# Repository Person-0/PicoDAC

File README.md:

# **PicoDAC**

<br>

*USB-C to 3.5mm HiFi mini DAC*

Fully custom PCB and 3D printed case.

## Design

### Preview Images
Note that a specially cut transparent acrylic sheet will be used as the top lid of the main PCB case which will be superglued to part of the case that is non-detachable.

The main PCB case also requires [this 2.5X8 screw](https://sharvielectronics.com/product/m2-5x8mm-phillips-head-mounting-screw-stainless-steel/) that will be used to attach the detachable part with the non-detachable part.

As for the case of the board - 2, since it really is just two directly connected USB-C plugs, the top and bottom part of the case will be glued together after seating the board-2 PCB inside it properly (after testing it).

<br>

All the design files are available in the [CAD folder](./CAD/).<br>
Exported STEP files for 3d-printing are available in [/CAD/exports](./CAD/exports/).

> Also note that the files:<br> 
> [1_PicoDAC_Case_DetachablePart.step](./CAD/exports/1_PicoDAC_Case_DetachablePart.step)<br>
> [2_PicoDAC_Case_Main.step](./CAD/exports/2_PicoDAC_Case_Main.step)<br>
> [3_board2_top_case.step](./CAD/exports/3_board2_top_case.step)<br>
> [4_board2_bottom_case.step](./CAD/exports/4_board2_bottom_case.step)<br>
> need to be printed as separate bodies.<br>
> All these files are also available in `.stl` format inside the [CAD/exports/stl_files](./CAD/exports/stl_files/) directory.

## **Motivation**

I recently bought a cheap USB-C to 3.5mm DAC and it was working perfectly fine until it broke.

I use my phone in bed a lot (yes i know this is a bad habit) vertically with the bottom of my phone resting on my chest. Since the USB-C port is at the bottom of my phone, anything connected to it has to do the heavy lifting of keeping the phone upright.

Naturally, the red part I've highlighted in the image slowly got bent and broke :(

To fix this issue, learn more about audio electronics, engineer a cool device and also make a higher-quality DAC in the process, I've started this project.

## **Hardware**
Main hardware components are:
- 1x CS43131-CNZR (A high-performance, 32-bit resolution, stereo audio DAC that supports up to 384-kHz sampling frequency with integrated low-noise ground-centered headphone amplifiers.): [LCSC part](https://www.lcsc.com/product-detail/C965907.html)
- XIAO RP2350 instead of the 2040 as it has integrated fractional dividers (also see: [this git issue](https://github.com/raspberrypi/pico-sdk/issues/1924))
- 9x SK6812 RGB LEDs for music level visualization

> **[View complete BOM](#bom)**

PCB Preview:

The complete schematics look like:

**Main Board:**

**Board 2:**

> Note that the PCB and schematic files can be opened using KiCAD. They are located in the `/hardware/PicoDAC` directory inside this repository.

Steps for viewing the PCB schematics and layout:
- Open KiCAD
- Click **File** (top left) >> **Open Project**
- Navigate to the the repository's saved destination,
- Open **/hardware/PicoDAC** directory
- Select the file `PicoDAC.kicad_pro`

## **Firmware**
*Checkout the [firmware directory](./firmware/) for the firmware README.md file and current status. It contains building, flashing instructions and also some special notes that might help with the process.*

## Ordering Parts, PCB/PCBA

I will be using JLCPCB along with their PCB Assembly service to get this PCB built assembled as it is the cheapest and best option available in my region.

Other than that, the only extra part is the **XIAO RP2350** MCU which is available on [robu.in](https://robu.in/).

> Note that the following PCB, PCBA costs are for 5 PCBs out of which 2 are assembled (this is the MOQ for JLCPCB) and also I have used basic components instead of extended wherever possible to reduce costs. 

### **BOM**
---

| S.No | Name                                 | Description                                        | Qty | Product URL                                                                     | Effective Cost ($) |
| ---: | ------------------------------------ | -------------------------------------------------- | --: | ------------------------------------------------------------------------------- | -----------------: |
|    1 | JLCPCB_PCB                           | PCB                                                |   1 | ~                                                                               |               7.00 |
|    2 | JLCPCB_Assembly                      | PCB Assembly                                       |   1 | ~                                                                               |              68.03 |
|    3 | JLCPCB_Shipping                      | Lowest price shipping: UPS Worldwide Express Saver |   1 | ~                                                                               |               9.10 |
|    4 | JLCPCB_Coupons                       | ~                                                  |   1 | ~                                                                               |             -10.00 |
|    5 | SeeedStudio XIAO RP2350              | MCU: XIAO RP2350                                   |   1 | [robu.in/...](https://robu.in/product/seeedstudio-xiao-rp2350-raspberry-pi-rp2350/) |               8.69 |
|    6 | Shipping for SeeedStudio XIAO RP2350 | Standard Shipping for XIAO RP2350                           |   1 | ~ |               0.51 |
|    5 | Acrylic Lid for Main Case            | Acrylic Laser Cutout (Qty = 2 as cost per piece is below 80INR and robu.in requires minimum cost to be atleast 80INR for non-metal laser cutting service order)                                  |   2 | ~ |               1.63 |
|    6 | Shipping for Acrylic Lid | Standard Shipping for Acrylic Lid                           |   1 | ~ |               0.51 |
|      |                                      |                                                    |     | **Total ($)**                                                                   |          **85.47** |
---

> The DXF file for the acrylic lid is available as [Main_Case_Lid_DoNotPrint.dxf](./CAD/exports/Main_Case_Lid_DoNotPrint.dxf) <br>
> Robu.in does not allow laser cutout service orders in the same cart as normal products, hence the two different 0.51$ shipping costs.

Please checkout the [/hardware/Ordering/](./hardware/Ordering/) directory to get the gerber, bom and cpl files to upload on JLC website.

## **References**
- All datasheets in [**BOM.csv**](./hardware/Ordering/bom.csv)
- https://datasheets.raspberrypi.com/rp2350/rp2350-datasheet.pdf
- https://github.com/raspberrypi/pico-sdk/issues/1924
- https://electronics.stackexchange.com/questions/336836/understanding-audio-jack-connection
- https://electronics.stackexchange.com/questions/95575/how-does-the-phone-detect-if-3-5-mm-jack-circuit-is-closed
- https://www.lcsc.com/product-detail/C33196.html
- https://www.lcsc.com/product-detail/C2867798.html (english version: https://www.ti.com/lit/ds/symlink/sn74axc4t245.pdf)
- https://www.totalphase.com/blog/2024/07/what-are-i2c-pull-up-resistors-calculate-their-values/
- https://forum.arduino.cc/t/why-use-a-47k-resistor-between-3-3v-and-sda-and-scl-port-of-esp3266/850553
- https://files.seeedstudio.com/wiki/XIAO-RP2350/res/Seeed-Studio-XIAO-RP2350-v1.0.pdf
- https://www.alldatasheet.com/datasheet-pdf/pdf/1265214/TI/TPS7A201825PDQNR.html
- https://wiki.seeedstudio.com/xiao_rp2350_arduino/
- https://forum.kicad.info/t/how-to-create-teardrops-in-pcb-editor/61920/
- https://electronics.stackexchange.com/questions/686845/pcb-design-question-power-plane-or-fat-traces-for-high-current
- https://www.eevblog.com/forum/eda/should-plane-be-used-to-connect-power-or-just-thicker-tracks/

## 😼💖

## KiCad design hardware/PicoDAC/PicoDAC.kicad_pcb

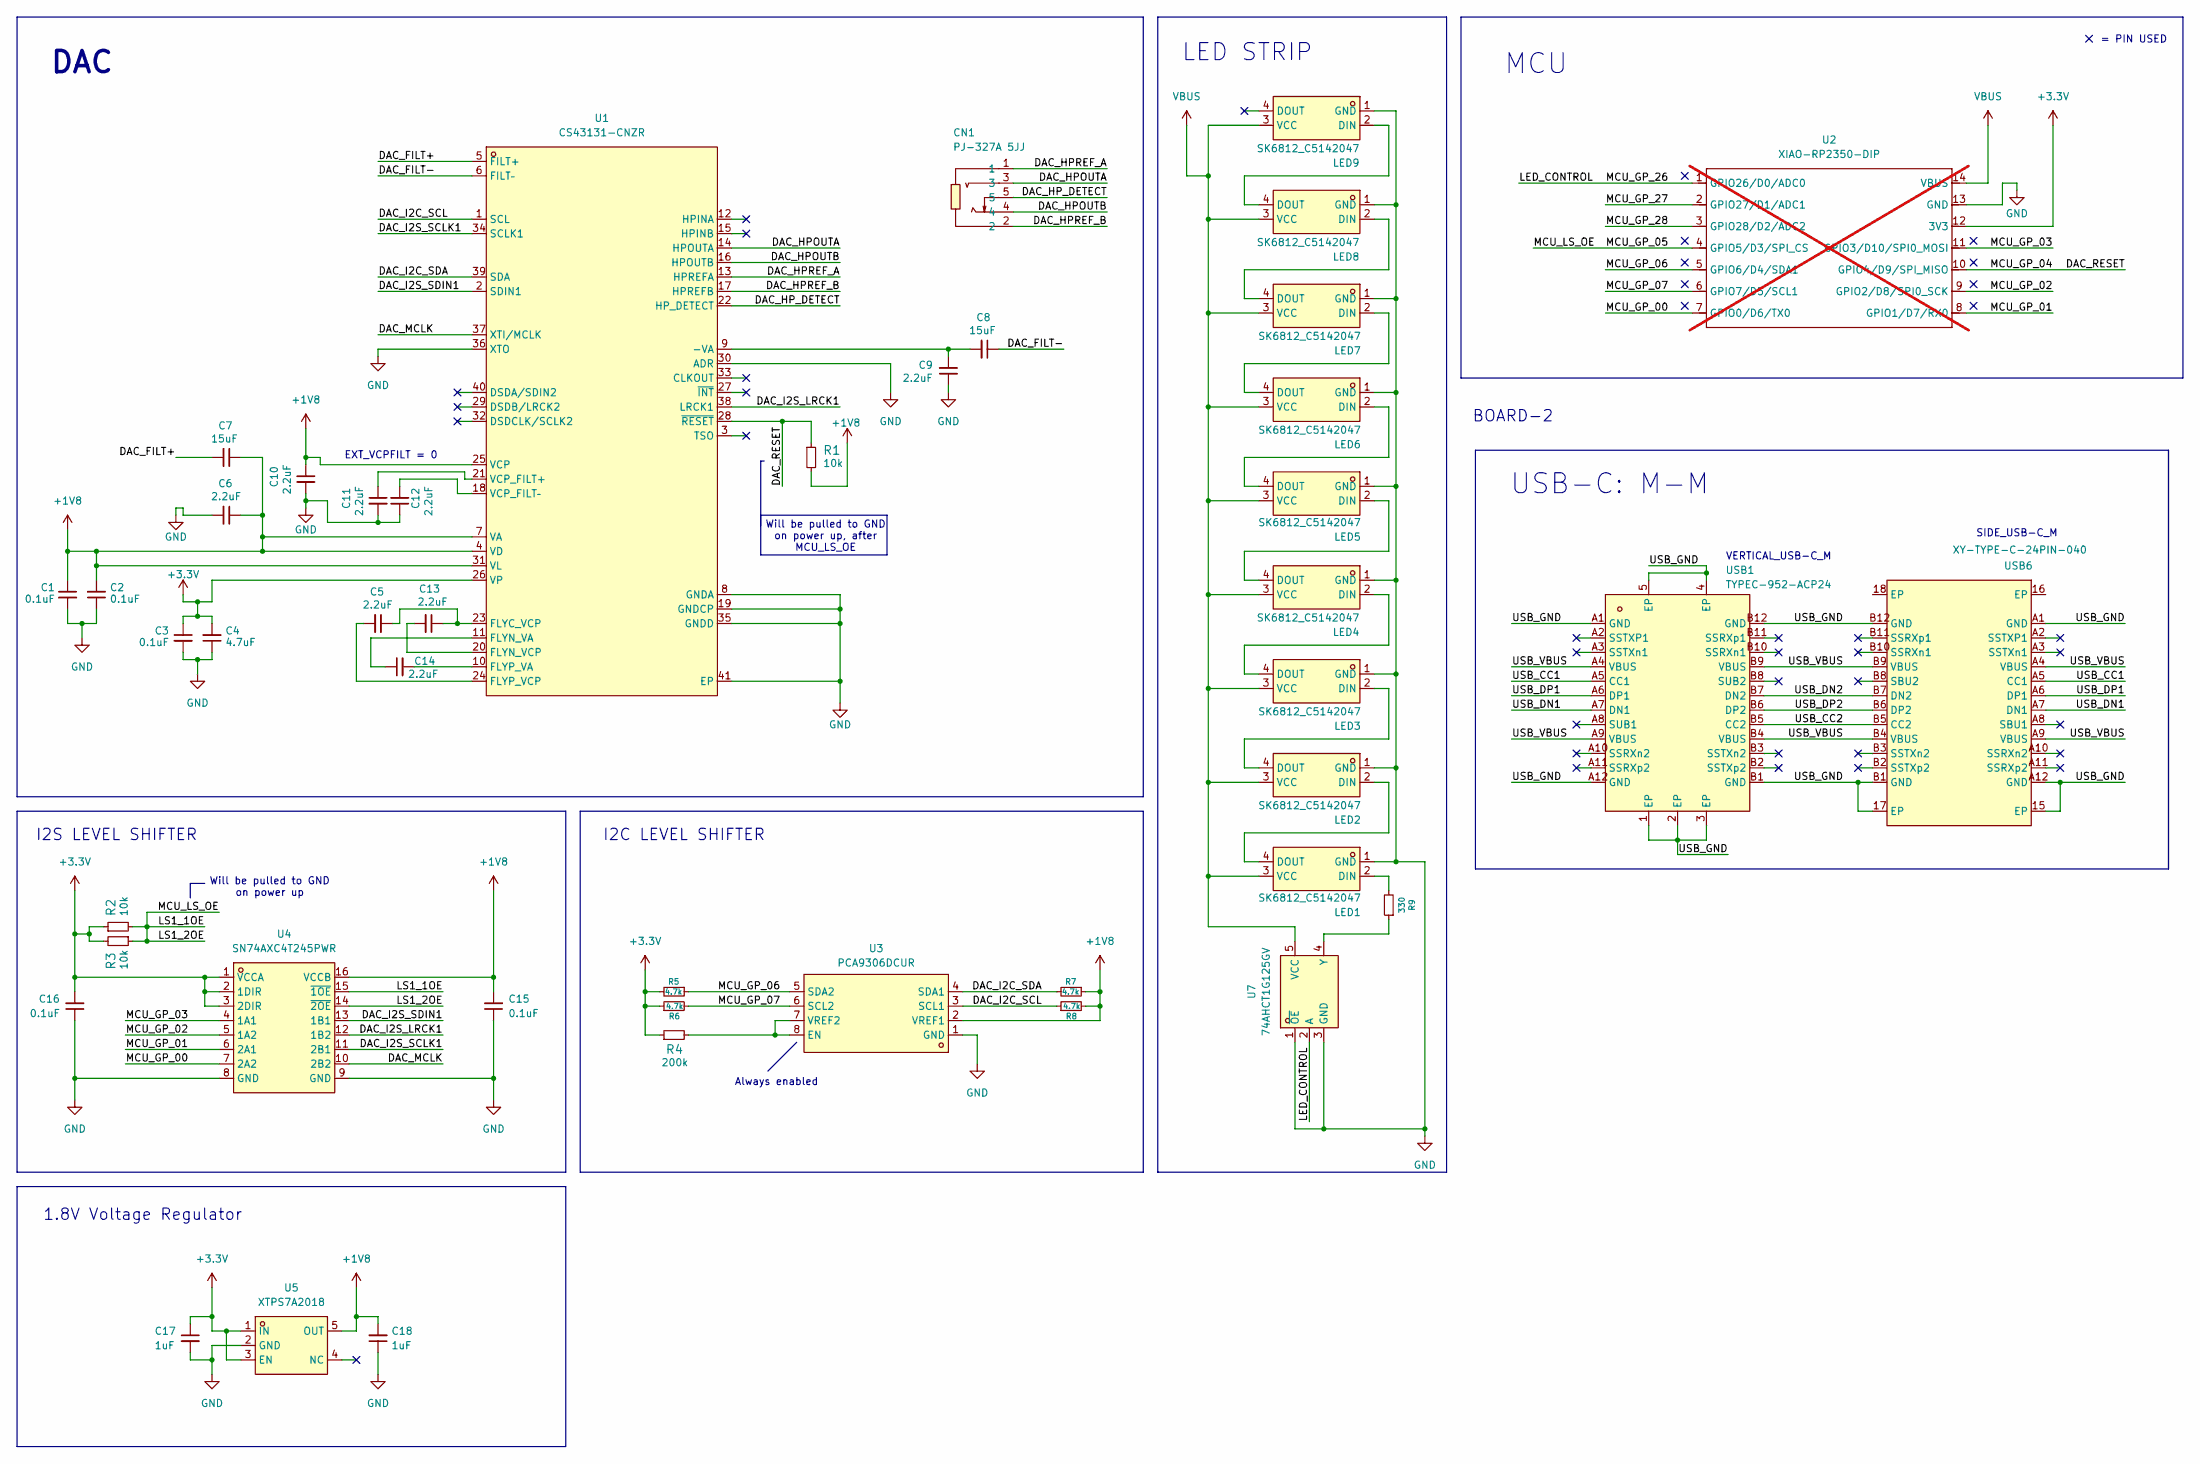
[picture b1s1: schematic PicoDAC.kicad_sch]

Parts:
C1, C2, C3, C15, C16: 0.1uF; C0402; MPN CL05B104KO5NNNC; LCSC Part C1525
C4: 4.7uF; C0603; MPN CL10A475KO8NNNC; LCSC Part C19666
C5, C6, C9, C10, C11, C12, C13, C14: 2.2uF; C0402; MPN CL05A225KO5NQNC; LCSC Part C170151
C7, C8: 15uF; C1210; MPN C3225X7R1C156MT000N; LCSC Part C694469
C17, C18: 1uF; C0402; MPN CL05A105KA5NQNC; LCSC Part C52923
CN1: PJ-327A 5JJ; AUDIO-SMD_PJ-327A5JJ; MPN PJ-327A 5JJ; LCSC Part C668605
LED1, LED2, LED3, LED4, LED5, LED6, LED7, LED8, LED9: SK6812_C5142047; LED-SMD_4P-L3.5-W2.8-BR-1; MPN SK6812SMINI-ER; LCSC Part C5142047
R1, R2, R3: 10k; R0402; MPN 0402WGF1002TCE; LCSC Part C25744
R4: 200k; R0402; MPN 0402WGF2003TCE; LCSC Part C25764
R5, R6, R7, R8: 4.7k; R0402; MPN 0402WGF4701TCE; LCSC Part C25900
R9: 330; R0402; MPN 0402WGF3300TCE; LCSC Part C25104
U1: CS43131-CNZR; TQFN-40_L5.0-W5.0-P0.40-TL-EP3.5; MPN CS43131-CNZR; LCSC Part C965907
U2: XIAO-RP2350-DIP; not fitted
U3: PCA9306DCUR; SSOP-8_L2.0-W2.3-P0.50-LS3.1-BR; MPN PCA9306DCUR; LCSC Part C33196
U4: SN74AXC4T245PWR; TSSOP-16_L5.0-W4.4-P0.65-LS6.4-BL; MPN SN74AXC4T245PWR; LCSC Part C2867798
U5: XTPS7A2018; SOT-23-5_L3.0-W1.7-P0.95-LS2.8-BL; MPN XTPS7A2018-XC; LCSC Part C51953293
U7: 74AHCT1G125GV; SOT-23-5_L3.0-W1.7-P0.95-LS2.8-BL; MPN 74AHCT1G125GV; LCSC Part C52140417
USB1: TYPEC-952-ACP24; USB-C-SMD_TYPEC-952-ACP24; MPN TYPEC-952-ACP24; LCSC Part C2840398
USB6: XY-TYPE-C-24PIN-040; USB-C-SMD_XY-TYPE-C-24PIN-040; MPN XY-TYPE-C-24PIN-040; LCSC Part C53133501

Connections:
+1V8: C1.1, C2.2, C6.1, C7.1, C10.1, C15.2, C18.2, R1.2, R7.1, R8.2, U1.4 (VD), U1.7 (VA), U1.25 (VCP), U1.31 (VL), U3.2 (VREF1), U4.16 (VCCB), U5.5 (OUT)
+3.3V: C3.1, C4.2, C16.2, C17.1, R2.1, R3.2, R4.1, R5.2, R6.1, U1.26 (VP), U2.12 (3V3), U4.1 (VCCA), U4.2 (1DIR), U4.3 (2DIR), U5.1 (IN), U5.3 (EN)
/DAC_FILT+: C7.2, U1.5 (FILT+)
/DAC_FILT-: C8.1, U1.6 (FILT–)
/DAC_HPOUTA: CN1.3, U1.14 (HPOUTA)
/DAC_HPOUTB: CN1.4, U1.16 (HPOUTB)
/DAC_HPREF_A: CN1.1, U1.13 (HPREFA)
/DAC_HPREF_B: CN1.2, U1.17 (HPREFB)
/DAC_HP_DETECT: CN1.5, U1.22 (HP_DETECT)
/DAC_I2C_SCL: R8.1, U1.1 (SCL), U3.3 (SCL1)
/DAC_I2C_SDA: R7.2, U1.39 (SDA), U3.4 (SDA1)
/DAC_I2S_LRCK1: U1.38 (LRCK1), U4.12 (1B2)
/DAC_I2S_SCLK1: U1.34 (SCLK1), U4.11 (2B1)
/DAC_I2S_SDIN1: U1.2 (SDIN1), U4.13 (1B1)
/DAC_MCLK: U1.37 (XTI/MCLK), U4.10 (2B2)
/DAC_RESET: R1.1, U1.28 (~RESET), U2.10 (GPIO4/D9/SPI_MISO)
/LED_CONTROL: U2.1 (GPIO26/D0/ADC0), U7.2 (A)
/LS1_1OE: R2.2, R3.1, U2.4 (GPIO5/D3/SPI_CS), U4.14 (~2OE), U4.15 (~1OE)
/MCU_GP_00: U2.7 (GPIO0/D6/TX0), U4.7 (2A2)
/MCU_GP_01: U2.8 (GPIO1/D7/RX0), U4.6 (2A1)
/MCU_GP_02: U2.9 (GPIO2/D8/SPI0_SCK), U4.5 (1A2)
/MCU_GP_03: U2.11 (GPIO3/D10/SPI0_MOSI), U4.4 (1A1)
/MCU_GP_06: R5.1, U2.5 (GPIO6/D4/SDA1), U3.5 (SDA2)
/MCU_GP_07: R6.2, U2.6 (GPIO7/D5/SCL1), U3.6 (SCL2)
/MCU_GP_27: U2.2 (GPIO27/D1/ADC1)
/MCU_GP_28: U2.3 (GPIO28/D2/ADC2)
/USB_CC1: USB1.A5 (CC1), USB6.A5 (CC1)
/USB_CC2: USB1.B5 (CC2), USB6.B5 (CC2)
/USB_DN1: USB1.A7 (DN1), USB6.A7 (DN1)
/USB_DN2: USB1.B7 (DN2), USB6.B7 (DN2)
/USB_DP1: USB1.A6 (DP1), USB6.A6 (DP1)
/USB_DP2: USB1.B6 (DP2), USB6.B6 (DP2)
/USB_GND: USB1.1 (EP), USB1.2 (EP), USB1.3 (EP), USB1.4 (EP), USB1.5 (EP), USB1.A1 (GND), USB1.A12 (GND), USB1.B1 (GND), USB1.B12 (GND), USB6.15 (EP), USB6.17 (EP), USB6.A1 (GND), USB6.A12 (GND), USB6.B1 (GND), USB6.B12 (GND)
/USB_VBUS: USB1.A4 (VBUS), USB1.A9 (VBUS), USB1.B4 (VBUS), USB1.B9 (VBUS), USB6.A4 (VBUS), USB6.A9 (VBUS), USB6.B4 (VBUS), USB6.B9 (VBUS)
GND: C1.2, C2.1, C3.2, C4.1, C6.2, C9.1, C10.2, C11.2, C12.1, C15.1, C16.1, C17.2, C18.1, LED1.1 (GND), LED2.1 (GND), LED3.1 (GND), LED4.1 (GND), LED5.1 (GND), LED6.1 (GND), LED7.1 (GND), LED8.1 (GND), LED9.1 (GND), U1.8 (GNDA), U1.19 (GNDCP), U1.30 (ADR), U1.35 (GNDD), U1.36 (XTO), U1.41 (EP), U2.13 (GND), U3.1 (GND), U4.8 (GND), U4.9 (GND), U5.2 (GND), U7.1 (~OE), U7.3 (GND)
unnamed: LED1.2 (DIN), R9.2
unnamed: LED1.4 (DOUT), LED2.2 (DIN)
unnamed: LED2.4 (DOUT), LED3.2 (DIN)
unnamed: LED3.4 (DOUT), LED4.2 (DIN)
unnamed: LED4.4 (DOUT), LED5.2 (DIN)
unnamed: LED5.4 (DOUT), LED6.2 (DIN)
unnamed: LED6.4 (DOUT), LED7.2 (DIN)
unnamed: LED7.4 (DOUT), LED8.2 (DIN)
unnamed: LED8.4 (DOUT), LED9.2 (DIN)
unnamed: C8.2, C9.2, U1.9 (-VA)
unnamed: C5.1, C13.1, U1.23 (FLYC_VCP)
unnamed: C14.1, U1.11 (FLYN_VA)
unnamed: C13.2, U1.20 (FLYN_VCP)
unnamed: C14.2, U1.10 (FLYP_VA)
unnamed: C5.2, U1.24 (FLYP_VCP)
unnamed: C11.1, U1.21 (VCP_FILT+)
unnamed: C12.2, U1.18 (VCP_FILT–)
unnamed: R4.2, U3.7 (VREF2), U3.8 (EN)
unnamed: R9.1, U7.4 (Y)
VBUS: LED1.3 (VCC), LED2.3 (VCC), LED3.3 (VCC), LED4.3 (VCC), LED5.3 (VCC), LED6.3 (VCC), LED7.3 (VCC), LED8.3 (VCC), LED9.3 (VCC), U2.14 (VBUS), U7.5 (VCC)

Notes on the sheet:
Will be pulled to GND on power up
I2S LEVEL SHIFTER
DAC
VERTICAL_USB-C_M
BOARD-2
= PIN USED
MCU
Will be pulled to GND on power up, after MCU_LS_OE
LED STRIP
EXT_VCPFILT = 0
I2C LEVEL SHIFTER
Always enabled
SIDE_USB-C_M
USB-C: M-M
1.8V Voltage Regulator

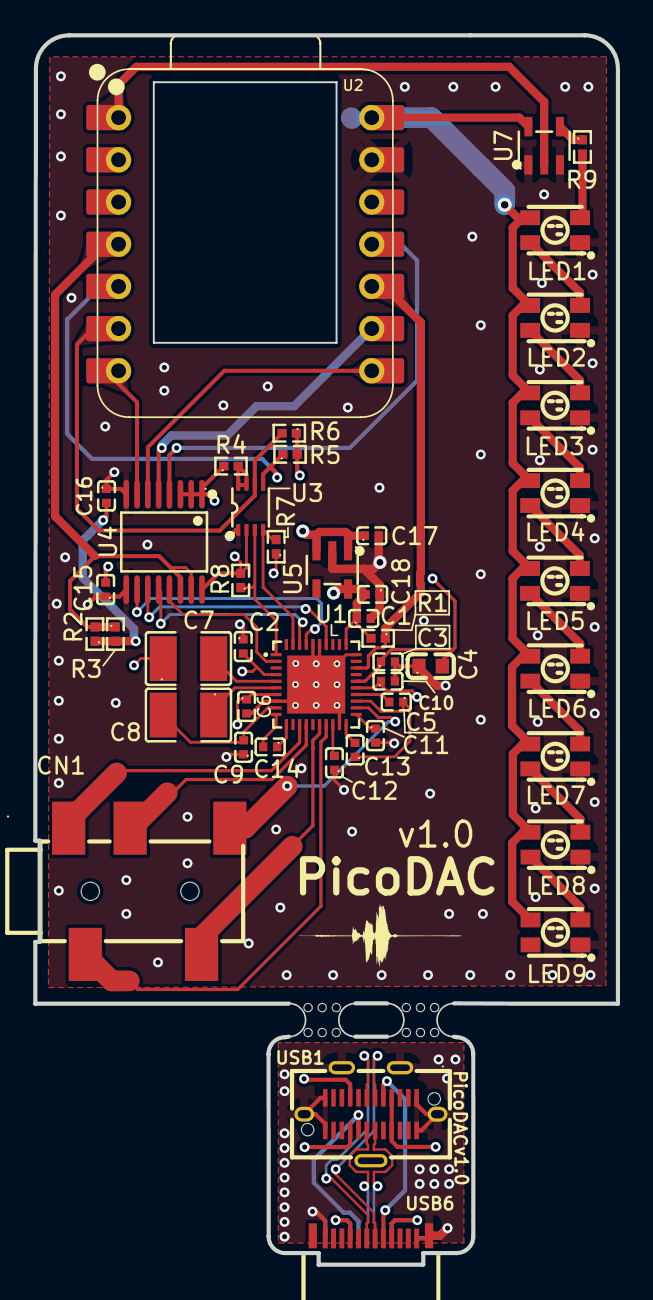
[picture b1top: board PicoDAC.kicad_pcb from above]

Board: 4 copper layers, 35.1 x 74.0 mm, 45 parts (0 on the bottom side), 53 nets.

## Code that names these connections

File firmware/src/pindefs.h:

// dac pins
#define PIN_DAC_MCLK                0
#define PIN_DAC_SCLK1               1
#define PIN_DAC_LRCK1               2
#define PIN_DAC_SDIN1               3
#define PIN_DAC_RESET               4
#define PIN_DAC_SDA                 6
#define PIN_DAC_SCL                 7

// level shifter output enable
#define PIN_MCU_LS_OE               5

// led pins
#define PIN_ONBOARD_NEOPIXEL        22
#define PIN_ONBOARD_NEOPIXEL_PWR    23
#define PIN_ONBOARD_LED             25

#define PIN_LED_CONTROL             26
